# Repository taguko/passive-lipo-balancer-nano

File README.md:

# passive-lipo-balancer-nano

A proof-of-technology passive LiPo cell balancer based on Arduino Nano.

This project monitors individual battery cell voltages and performs passive balancing by selectively discharging cells through resistors. It is intended for educational, research, and hobby robotics applications.

The firmware currently focuses on two practical operating modes:

- **Storage Mode**: Automatically discharges all cells to a storage voltage of approximately **3.8 V per cell**.
- **Balance Mode**: Discharges higher-voltage cells until all cells match the voltage of the lowest cell in the pack.

The goal of this project is to provide a simple and easy-to-understand platform for learning battery management and cell balancing techniques.

## Features

- Individual cell voltage monitoring
- Passive balancing using discharge resistors
- Storage Mode (~3.8 V/cell)
- Balance Mode (equalize all cells to the lowest cell voltage)
- Arduino Nano (ATmega328P) based design
- Simple and low-cost hardware implementation
- Open-source hardware and firmware
- Suitable for Li-ion and LiPo battery packs

## Hardware

### Main Components

- Arduino Nano (ATmega328P)
- Cell voltage sensing circuits
- MOSFETs for discharge control
- Discharge resistors
- Battery balance connector
- Status OLED (optional)

### Circuit Architecture

The Arduino Nano can be powered from USB at any time. When JP1 is installed, the Cell2+ node (approximately 7.4–8.4 V) is additionally connected to the Nano VIN pin, allowing standalone operation from the battery pack. USB power remains available regardless of the JP1 setting.

Cell voltages are measured through resistor dividers, while individual cells are balanced by switching dedicated MOSFET-resistor discharge paths.

```mermaid
flowchart LR

    USB["USB 5 V"]

    Battery["2S / 3S LiPo Pack"]
    Cell2["Cell2+<br/>(≈7.4–8.4 V)"]

    JP1["JP1"]

    subgraph Nano["Arduino Nano"]
        USB5V["USB Power Input"]
        VIN["VIN"]

        MCU["ATmega328P"]

        ADC["ADC Inputs<br/>A0-A2"]

        CTRL["Balancing Outputs<br/>D2-D4"]

        I2C["I²C"]
    end

    subgraph Sense["Voltage Sensing"]
        V1["Cell1 Divider"]
        V2["Cell1+Cell2 Divider"]
        V3["Cell1+Cell2+Cell3 Divider"]
    end

    subgraph Balance["Passive Balancing"]
        B1["Cell1<br/>33Ω + NMOS"]
        B2["Cell2<br/>33Ω + NMOS"]
        B3["Cell3<br/>33Ω + NMOS"]
    end

    OLED["OLED Display"]
    SW["Mode Switch"]

    USB --> USB5V

    Cell2 --> JP1
    JP1 --> VIN

    Battery --> V1
    Battery --> V2
    Battery --> V3

    V1 --> ADC
    V2 --> ADC
    V3 --> ADC

    CTRL --> B1
    CTRL --> B2
    CTRL --> B3

    I2C <--> OLED
    SW --> MCU
```

### Control Flow

```mermaid
flowchart TD

    START([Loop Start])

    OFF["Turn All Discharge MOSFETs OFF"]

    MEASURE["Measure A0, A1, A2"]

    CALC["Calculate Individual Cell Voltages<br/><br/>Cell1 = A0<br/>Cell2 = A1 - A0<br/>Cell3 = A2 - A1"]

    DISPLAY["Update Serial Output<br/>and OLED Display"]

    MODE{"Mode Switch"}

    STORAGE["Storage_discharge()"]

    BALANCE["Balance_discharge()"]

    WAIT["Wait Until 20 ms Cycle Elapses"]

    START --> OFF
    OFF --> MEASURE
    MEASURE --> CALC
    CALC --> DISPLAY
    DISPLAY --> MODE

    MODE -->|HIGH| STORAGE
    MODE -->|LOW| BALANCE

    STORAGE --> WAIT
    BALANCE --> WAIT

    WAIT --> START
```

### Cell Voltage Reconstruction
```mermaid
flowchart LR

    A0["ADC A0<br/>Cell1"]
    A1["ADC A1<br/>Cell1 + Cell2"]
    A2["ADC A2<br/>Cell1 + Cell2 + Cell3"]

    C1["Cell1 Voltage"]
    C2["Cell2 Voltage"]
    C3["Cell3 Voltage"]

    A0 -->|"Direct"| C1

    A1 -->|"A1 - A0"| C2

    A2 -->|"A2 - A1"| C3
```

### BOM
[PartsCabi.net](https://partscabi.net/list/e6f96d02-e6a8-4c4d-9230-7bf2f09aacb4)

## Operating Modes

### Storage Mode

Storage Mode is intended for preparing LiPo battery packs for long-term storage.

The balancer discharges cells until each cell reaches approximately **3.8 V**, which is commonly considered a suitable storage voltage for LiPo batteries.

### Balance Mode

Balance Mode reduces voltage differences between cells.

The firmware identifies the cell with the lowest voltage and selectively discharges higher-voltage cells until all cells reach approximately the same voltage.

## Safety Notice

This project works directly with rechargeable lithium-based batteries.

Improper handling of Li-ion or LiPo batteries may result in overheating, fire, property damage, or personal injury.

Always:

- Verify connections before powering the circuit
- Use appropriate fuses and wiring
- Monitor batteries during testing
- Never leave batteries unattended while charging or balancing

The author assumes no responsibility for any damage, injury, or loss resulting from the use of this project.

## Project Status

⚠️ This is an experimental proof-of-technology project.

The hardware and firmware are under active development and should not be considered a certified battery management system (BMS).

## Contributing

Contributions, bug reports, and suggestions are welcome.

Feel free to open an issue or submit a pull request.

## License

This project is licensed under the MIT License.

See the `LICENSE` file for details.

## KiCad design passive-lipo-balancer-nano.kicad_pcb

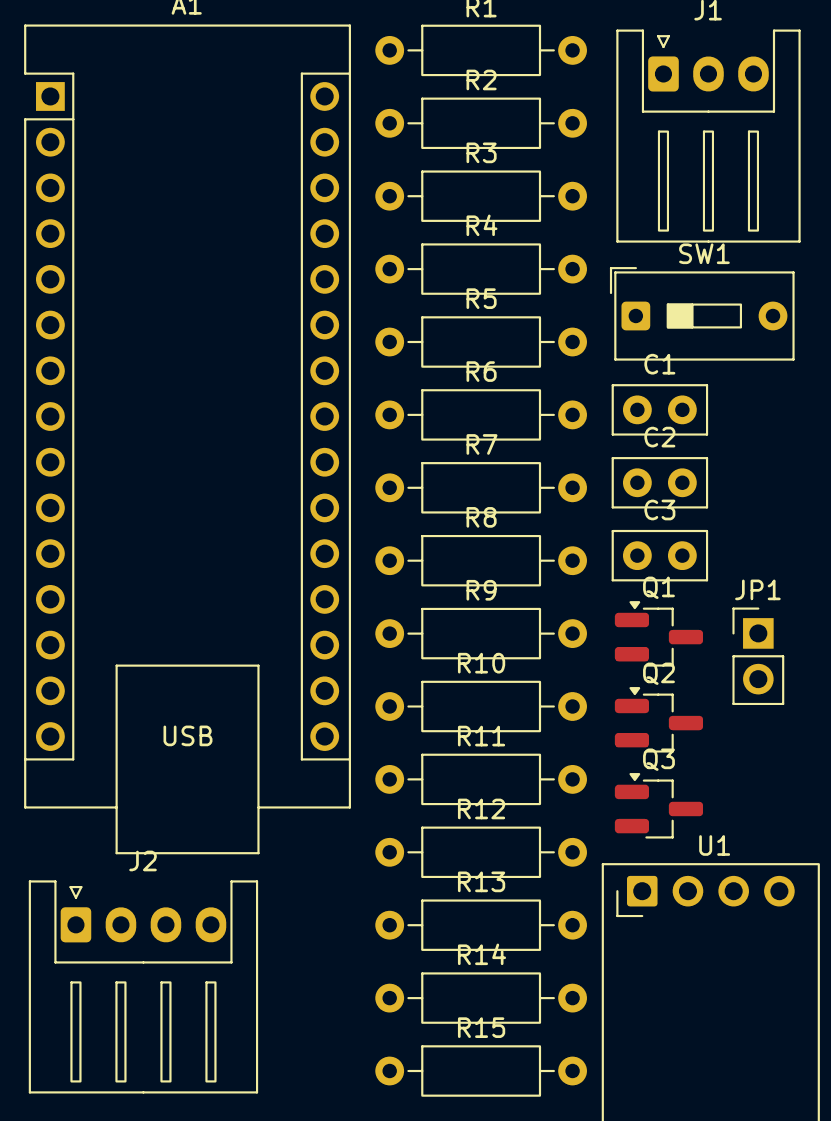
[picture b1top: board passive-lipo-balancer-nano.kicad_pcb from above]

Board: 2 copper layers, 27 parts (0 on the bottom side), 21 nets, no tracks yet.

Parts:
A1: Arduino_Nano_v3.x; Arduino_Nano
C1, C2, C3: 100nF; C_Disc_D5.0mm_W2.5mm_P2.50mm
J1: Conn_01x03; JST_XH_S3B-XH-A_1x03_P2.50mm_Horizontal
J2: Conn_01x04; JST_XH_S4B-XH-A_1x04_P2.50mm_Horizontal
JP1: Jumper_2_Open; PinHeader_1x02_P2.54mm_Vertical
Q1, Q2, Q3: MTN2306AN3; SOT-23_Handsoldering
R1, R2, R3, R13, R14, R15: 100kΩ; R_Axial_DIN0207_L6.3mm_D2.5mm_P10.16mm_Horizontal
R4, R5, R6: 8k2Ω; R_Axial_DIN0207_L6.3mm_D2.5mm_P10.16mm_Horizontal
R7, R8, R9: 1W33Ω; R_Axial_DIN0207_L6.3mm_D2.5mm_P10.16mm_Horizontal
R10, R11, R12: 1kΩ; R_Axial_DIN0207_L6.3mm_D2.5mm_P10.16mm_Horizontal
SW1: SW_DIP_x01; SW_DIP_SPSTx01_Slide_9.78x4.72mm_W7.62mm_P2.54mm
U1: ER_OLEDM0.91_1x-I2C

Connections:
+5V: A1.27 (+5V), U1.2 (VCC)
Cell1+: J1.2, J2.3, R1.1, R7.2
Cell2+: J1.1, J2.2, JP1.1 (A), R2.1, R8.2
Cell3+: J2.1, R3.1, R9.2
GND: A1.4 (GND), A1.29 (GND), C1.2, C2.2, C3.2, J1.3, J2.4, Q1.2 (S), Q2.2 (S), Q3.2 (S), R4.2, R5.2, R6.2, R13.1, R14.1, R15.1, SW1.1, U1.1 (GND)
unnamed: A1.11 (D8), SW1.2
unnamed: A1.30 (VIN), JP1.2 (B)
unnamed: Q1.3 (D), R7.1
unnamed: Q1.1 (G), R10.1, R13.2
unnamed: Q2.3 (D), R8.1
unnamed: Q2.1 (G), R11.1, R14.2
unnamed: Q3.3 (D), R9.1
unnamed: Q3.1 (G), R12.1, R15.2
SCL: A1.24 (A5), U1.3 (SCL)
SDA: A1.23 (A4), U1.4 (SDA)
Sink_Cell1: A1.5 (D2), R10.2
Sink_Cell2: A1.6 (D3), R11.2
Sink_Cell3: A1.7 (D4), R12.2
V_Cell1: A1.19 (A0), C1.1, R3.2, R6.1
V_Cell2: A1.20 (A1), C2.1, R2.2, R5.1
V_Cell3: A1.21 (A2), C3.1, R1.2, R4.1

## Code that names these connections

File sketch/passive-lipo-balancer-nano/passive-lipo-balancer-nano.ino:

// passive-lipo-balancer-nano

// OLED
#include "oled.h"
#include <Adafruit_GFX.h>
#include <Adafruit_SSD1306.h>

const float voltage_storage = 3.80;

const float allowable_error = 0.005;

const uint32_t cycle = 20;  // [ms]

const float R1 = 100000;
const float R2 = 8200;
const float voltage_division_ratio = R2 / (R2 + R1);

const int SW1 = 8;

const int Sink_Cell1 = 2;
const int Sink_Cell2 = 3;
const int Sink_Cell3 = 4;

const int V_Cell1 = A0;
const int V_Cell2 = A1;
const int V_Cell3 = A2;

float voltage_cell[] = { 0, 0, 0 };

Adafruit_SSD1306 display(SCREEN_WIDTH, SCREEN_HEIGHT, &Wire, OLED_RESET);

void setup() {
  // Serial Port
  Serial.begin(9600);

  // pinMode
  analogReference(INTERNAL);  // 1V1

  pinMode(SW1, INPUT_PULLUP);

  pinMode(Sink_Cell1, OUTPUT);
  pinMode(Sink_Cell2, OUTPUT);
  pinMode(Sink_Cell3, OUTPUT);

  pinMode(V_Cell1, INPUT);
  pinMode(V_Cell2, INPUT);
  pinMode(V_Cell3, INPUT);

  pinMode(LED_BUILTIN, OUTPUT);

  // setup
  oled_setup();
}

void loop() {
  uint32_t preMillis = millis();

  // Ready
  digitalWrite(Sink_Cell1, LOW);
  digitalWrite(Sink_Cell2, LOW);
  digitalWrite(Sink_Cell3, LOW);

  // Voltage check
  voltage_cell[0] = mapf(analogRead(V_Cell1), 0, 1023, 0, 1.1) / voltage_division_ratio;
  voltage_cell[1] = mapf(analogRead(V_Cell2) - analogRead(V_Cell1), 0, 1023, 0, 1.1) / voltage_division_ratio;
  voltage_cell[2] = mapf(analogRead(V_Cell3) - analogRead(V_Cell2), 0, 1023, 0, 1.1) / voltage_division_ratio;
  serial_handle();
  oled_handle();

  // Mode choose & run discharge
  if (digitalRead(SW1) == HIGH)
    Storage_discharge();
  else
    Balance_discharge();

  // Wait
  while ((millis() - preMillis) < cycle)
    ;
}

void serial_handle() {
  if (digitalRead(SW1) == HIGH)
    Serial.print("Balance mode ");
  else
    Serial.print("Storage mode ");
  String info;
  info = "V_Cell1:" + String(voltage_cell[0]) + "V ";
  Serial.print(info);
  info = "V_Cell2:" + String(voltage_cell[1]) + "V ";
  Serial.print(info);
  info = "V_Cell3:" + String(voltage_cell[2]) + "V";
  Serial.println(info);
}

float mapf(float x, float in_min, float in_max,
           float out_min, float out_max) {
  return (x - in_min) * (out_max - out_min)
           / (in_max - in_min)
         + out_min;
}
